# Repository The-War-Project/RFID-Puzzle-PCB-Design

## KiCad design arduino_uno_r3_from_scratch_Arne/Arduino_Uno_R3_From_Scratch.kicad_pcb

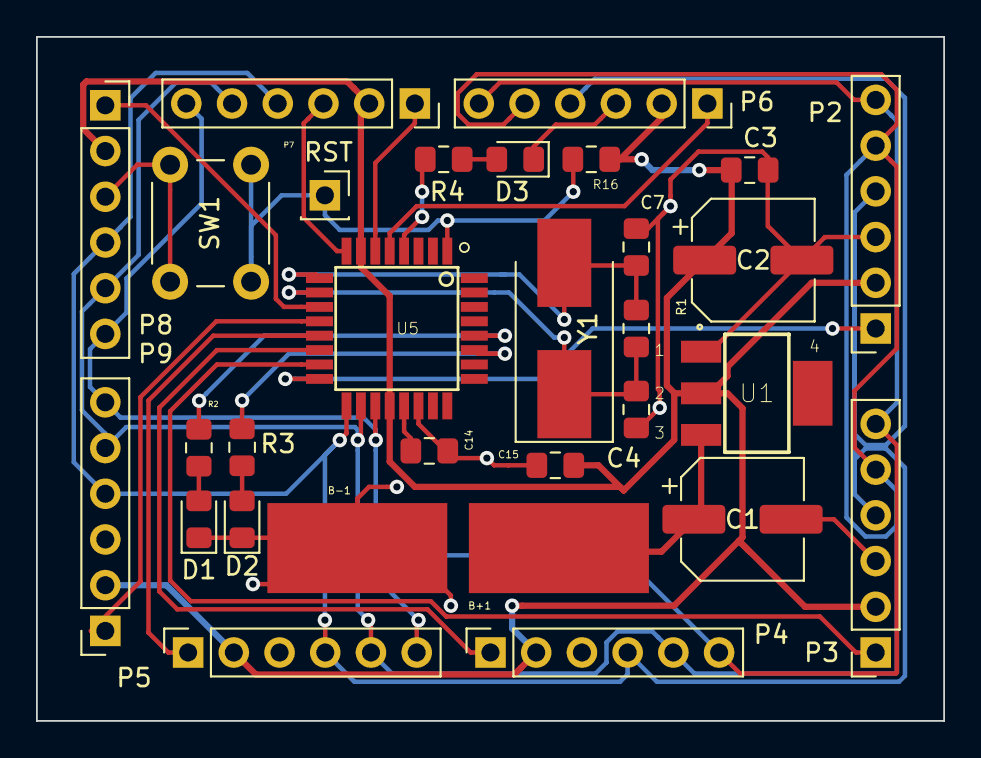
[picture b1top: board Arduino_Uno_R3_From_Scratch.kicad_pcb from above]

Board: 2 copper layers, 50.4 x 38.0 mm, 30 parts (0 on the bottom side), 24 nets.

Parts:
B+1: Conn_01x01; SolderWirePad_1x01_SMD_5x10mm
B-1: Conn_01x01; SolderWirePad_1x01_SMD_5x10mm
C1, C2: 47uF; CP_Elec_6.3x5.8
C3, C14, C15: 0.1 uF; C_0805_2012Metric_Pad1.15x1.40mm_HandSolder
C4, C7: 20p; C_0805_2012Metric_Pad1.15x1.40mm_HandSolder
D1, D2, D3: LED; LED_0805_2012Metric_Pad1.15x1.40mm_HandSolder
P2, P3, P4, P5, P6, P7, P8, P9: CONN_01X06; PinSocket_1x06_P2.54mm_Vertical
R1: 1M; R_0805_2012Metric_Pad1.15x1.40mm_HandSolder
R2, R3, R4: 470; R_0805_2012Metric_Pad1.15x1.40mm_HandSolder
R16: 10K; R_0805_2012Metric_Pad1.15x1.40mm_HandSolder
RST: Conn_01x01; PinSocket_1x01_P2.54mm_Vertical
SW1: RESET_SWITCH; SW_PUSH_6mm_H7.3mm
U1: LD1117S50TR; SOT223
U5: ATMEGA328P; QFP80P900X900X120-32N
Y1: Crystal; Crystal_SMD_7050-2Pin_7.0x5.0mm_HandSoldering

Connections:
5V_LDO: C2.1, C3.1, C15.1, P2.2, P3.2, P4.2, P5.2, P6.2, P7.2, P8.2, P9.2, R16.2, U1.2, U5.7, U5.20
328P_ICSP_MISO: P2.5, P3.5, P4.5, P5.5, P6.5, P7.5, P8.5, P9.5, U5.18
328P_ICSP_MOSI: P2.4, P3.4, P4.4, P5.4, P6.4, P7.4, P8.4, P9.4, U5.17
328P_ICSP_SCK: P2.6, P3.6, P4.6, P5.6, P6.6, P7.6, P8.6, P9.6, U5.19
/ATMEGA328P/328P_RESET: R16.1, RST.1, SW1.2, U5.1
/ATMEGA328P/ARD_DIG3: P6.1, U5.5
/ATMEGA328P/ARD_DIG4: P7.1, U5.6
/ATMEGA328P/ARD_DIG5: P8.1, U5.11
/ATMEGA328P/ARD_DIG6: P9.1, U5.12
/ATMEGA328P/ARD_DIG7: P5.1, U5.13
/ATMEGA328P/ARD_DIG8: P4.1, U5.14
/ATMEGA328P/ARD_DIG9: P3.1, U5.15
/ATMEGA328P/ARD_DIG10/SPI_SS: P2.1, U5.16
GND: B-1.1, C1.2, C2.2, C3.2, C4.2, C7.2, C14.2, C15.2, D1.1, D2.1, D3.1, P2.3, P3.3, P4.3, P5.3, P6.3, P7.3, P8.3, P9.3, SW1.1, U1.1, U5.8, U5.22
unnamed: C4.1, R1.1, U5.10, Y1.1
unnamed: C7.1, R1.2, U5.9, Y1.2
unnamed: C14.1, U5.21
unnamed: D1.2, R2.1
unnamed: D2.2, R3.2
unnamed: D3.2, R4.1
unnamed: R2.2, U5.28
unnamed: R3.1, U5.27
unnamed: R4.2, U5.4
Vin: B+1.1, C1.1, U1.3

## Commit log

2020-05-05 PCB RFID
